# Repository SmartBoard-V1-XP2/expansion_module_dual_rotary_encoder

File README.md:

# Dual Encoder Module with ATtiny48

## Overview
This repository is dedicated to the design and implementation of a Dual Encoder Module, featuring two EC12E24204A8 encoders interfaced with an ATtiny48 microcontroller. Designed as an expansion module for the smartboard, it connects via a single smartboard connector, providing precise rotational input control for a wide range of applications.

## Key Features
- **Dual EC12E24204A8 Encoders**: High-quality rotary encoders for accurate and reliable input.
- **ATtiny48 Microcontroller**: Efficiently decodes and manages encoder signals.
- **SPI/UART Communication**: Offers flexible data transfer options to suit different requirements.
- **Smartboard Compatibility**: Easily integrates with smartboard systems through a dedicated connector.
- **Programmable via Connector Signals**: Enables easy programming and configuration.

### Schematic

*The schematic diagram provides a detailed view of the circuit design and component connections, essential for understanding the module's functionality and for troubleshooting.*

### Board Design - Top View

*This image shows the top view of the PCB layout, highlighting the placement of components, including the encoders and the ATtiny48 microcontroller.*

### Board Design - Bottom View

*The bottom view of the PCB layout illustrates the routing of traces and the arrangement of additional components, giving a complete overview of the PCB design.*

### Connector Signals

*This diagram details the signal configuration on the connector used to interface the module with a smartboard, outlining each pin's function and connectivity.*

## Contributions and Feedback
Contributions to this project are welcome. If you have suggestions for improvement or have developed additional features, please fork the repository, make your changes, and submit a pull request. For any questions or issues, please open an issue in the GitHub repository.

## License
This charger project is licensed under the MIT License with the following terms:

- **Permission to Use**: You are free to use, modify, and distribute this charger design in both private and commercial settings.
- **Attribution Requirement**: While not required, attribution to the original author, Adam Łuczak, is appreciated. This can be done through a citation or a link back to this repository.
- **No Warranty**: This design is provided "as is", without warranty of any kind. Use it at your own risk.
- **Liability**: The author is not liable for any damages or losses that may arise from the use of this design.

For the full terms and conditions, please refer to the MIT License documentation.

## Contact
Should you have any inquiries or suggestions regarding this charger project, please don't hesitate to contact Adam Łuczak at adam.luczak@outlook.com.

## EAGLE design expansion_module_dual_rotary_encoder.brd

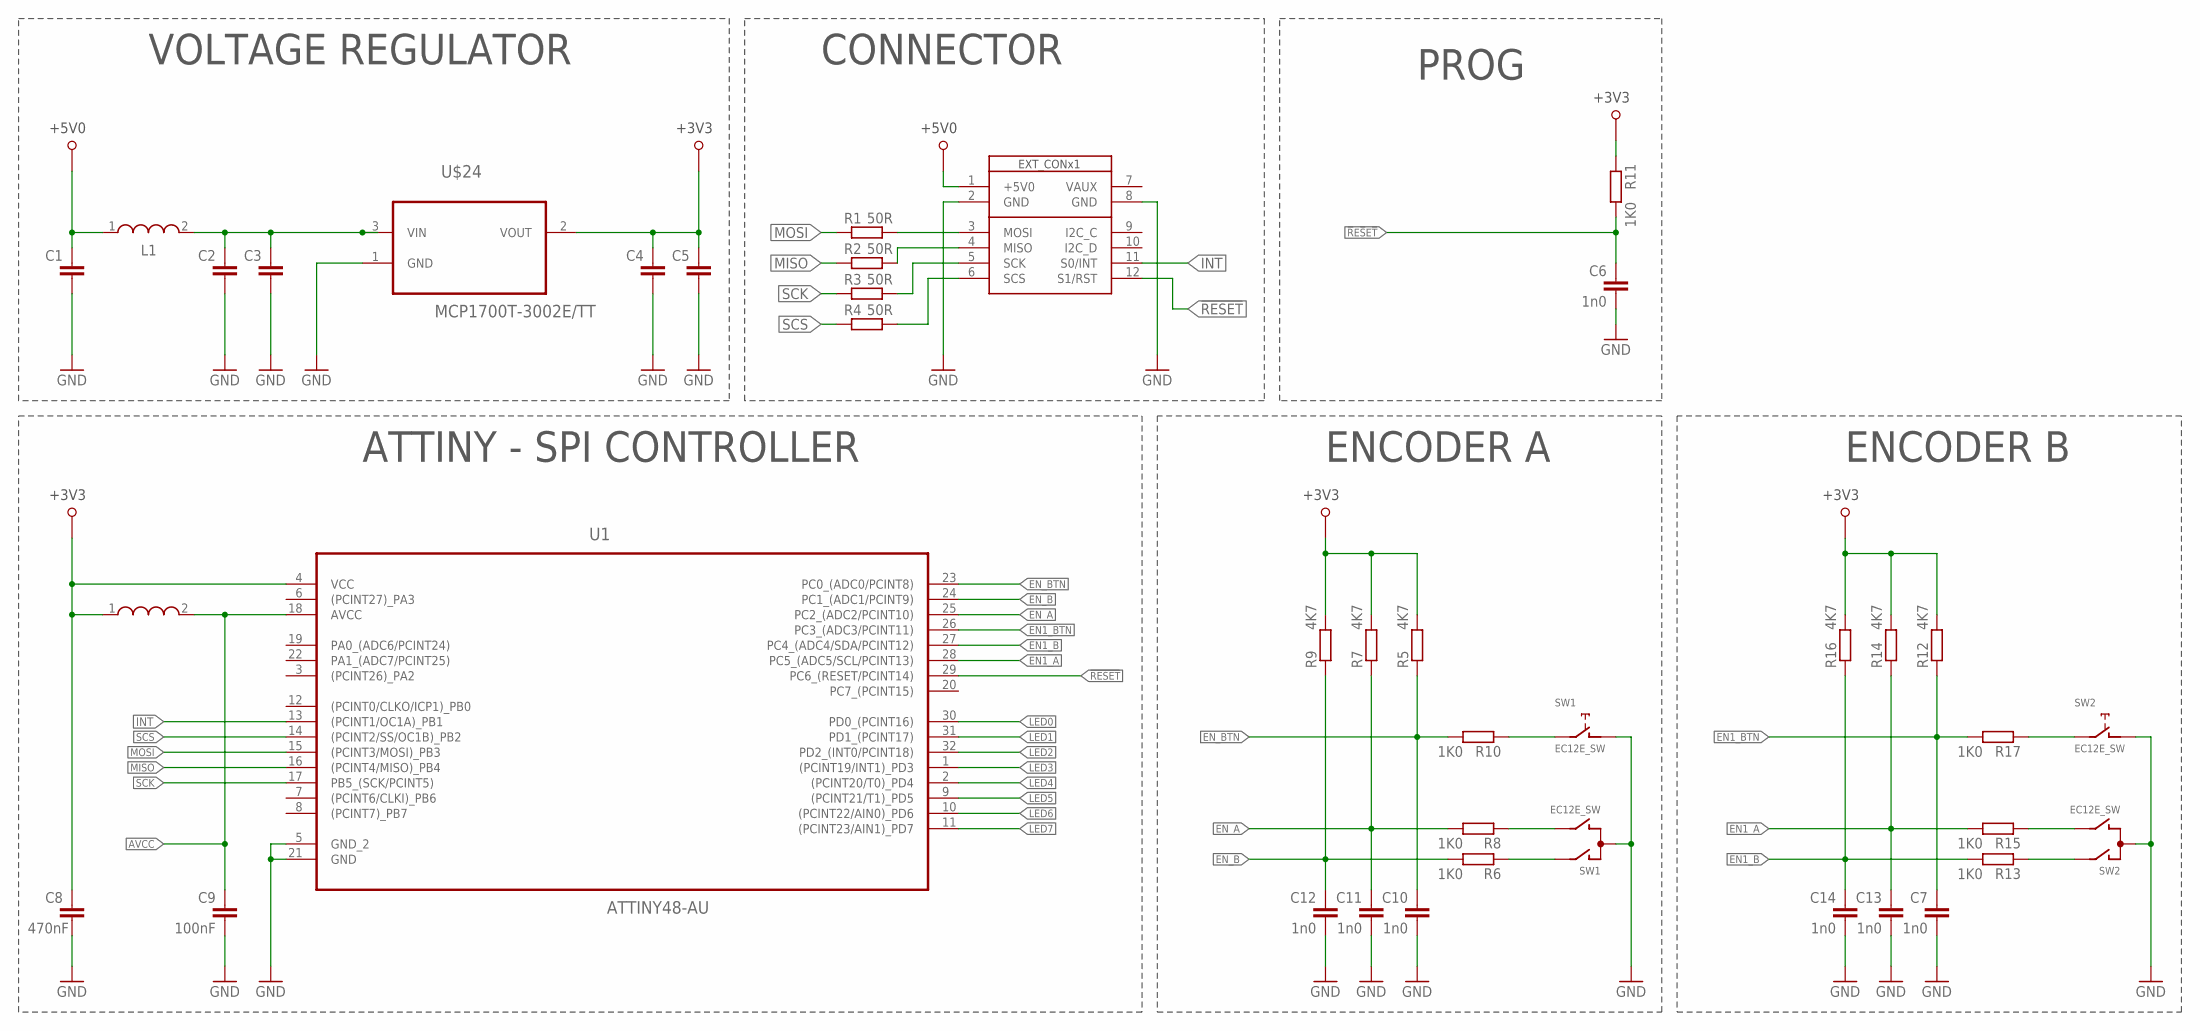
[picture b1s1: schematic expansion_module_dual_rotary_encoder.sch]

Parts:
C1, C2, C3, C4, C5: C-EUC0805; C0805
C6, C7, C10, C11, C12, C13, C14: 1n0; C0805
C8: 470nF; C0805
C9: 100nF; C0805
L1: WE-LQ_1210; WE-LQ_M
L2: WE-PMI_0805
R1, R2, R3, R4: 50R; R0805
R5, R7, R9, R12, R14, R16: 4K7; R0805
R6, R8, R10, R11, R13, R15, R17: 1K0; R0805
SW1, SW2: EC12E_SW; ALPS_EC12E_SW
U1: ATTINY48-AU; QFP80P900X900X120-32N
U$1: SB_EXT_CON_X1_SPI; SB_EXT_CON_X1_FULL
U$24: MCP1700T-3002E/TT; SOT95P237X112-3N

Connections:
!R!E!S!E!T: C6.2, R11.2
!RESET: U1.29 (PC6_(RESET/PCINT14)), U$1.12 (S1/RST)
+3V3: C4.2, C5.2, C8.2, L2.1, R5.2, R7.2, R9.2, R11.1, R12.2, R14.2, R16.2, U1.4 (VCC), U$24.2 (VOUT)
+5V0: C1.2, L1.1, U$1.1 (+5V0)
AVCC: C9.2, L2.2, U1.18 (AVCC)
EN1_A: C13.2, R14.1, R15.2, U1.28 (PC5_(ADC5/SCL/PCINT13))
EN1_B: C14.2, R13.2, R16.1, U1.27 (PC4_(ADC4/SDA/PCINT12))
EN1_BTN: C7.2, R12.1, R17.2, U1.26 (PC3_(ADC3/PCINT11))
EN_A: C11.2, R7.1, R8.2, U1.25 (PC2_(ADC2/PCINT10))
EN_B: C12.2, R6.2, R9.1, U1.24 (PC1_(ADC1/PCINT9))
EN_BTN: C10.2, R5.1, R10.2, U1.23 (PC0_(ADC0/PCINT8))
GND: C1.1, C2.1, C3.1, C4.1, C5.1, C6.1, C7.1, C8.1, C9.1, C10.1, C11.1, C12.1, C13.1, C14.1, SW1.C, SW1.D (1), SW2.C, SW2.D (1), U1.5 (GND_2), U1.21 (GND), U$1.2 (GND), U$1.8 (GND), U$24.1 (GND)
INT: U1.13 ((PCINT1/OC1A)_PB1), U$1.11 (S0/INT)
LED0: U1.30 (PD0_(PCINT16))
LED1: U1.31 (PD1_(PCINT17))
LED2: U1.32 (PD2_(INT0/PCINT18))
LED3: U1.1 ((PCINT19/INT1)_PD3)
LED4: U1.2 ((PCINT20/T0)_PD4)
LED5: U1.9 ((PCINT21/T1)_PD5)
LED6: U1.10 ((PCINT22/AIN0)_PD6)
LED7: U1.11 ((PCINT23/AIN1)_PD7)
MISO: R2.1, U1.16 ((PCINT4/MISO)_PB4)
MOSI: R1.1, U1.15 ((PCINT3/MOSI)_PB3)
unnamed: R1.2, U$1.3 (MOSI)
unnamed: R2.2, U$1.4 (MISO)
unnamed: R3.2, U$1.5 (SCK)
unnamed: R4.2, U$1.6 (SCS)
unnamed: R6.1, SW1.A
unnamed: R13.1, SW2.A
unnamed: C2.2, C3.2, L1.2, U$24.3 (VIN)
unnamed: R15.1, SW2.B
unnamed: R8.1, SW1.B
unnamed: R10.1, SW1.E (2)
unnamed: R17.1, SW2.E (2)
SCK: R3.1, U1.17 (PB5_(SCK/PCINT5))
SCS: R4.1, U1.14 ((PCINT2/SS/OC1B)_PB2)

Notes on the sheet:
CONNECTOR
VOLTAGE REGULATOR
ATTINY - SPI CONTROLLER
ENCODER A
PROG
ENCODER B

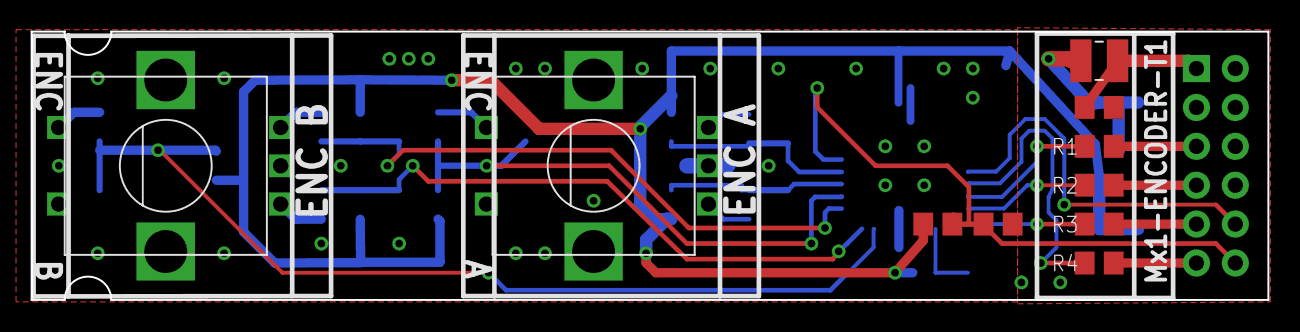
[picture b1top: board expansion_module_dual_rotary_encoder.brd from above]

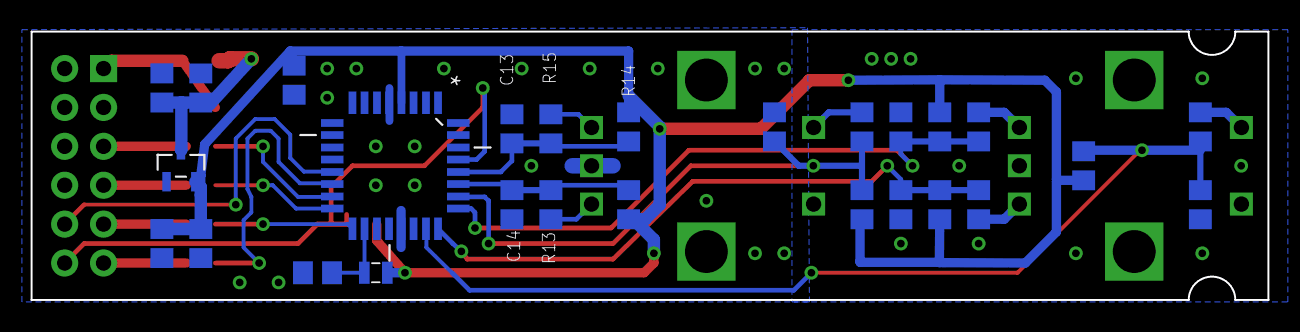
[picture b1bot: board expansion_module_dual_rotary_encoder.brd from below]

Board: 2 copper layers, 80.8 x 17.5 mm, 38 parts (27 on the bottom side), 28 nets.

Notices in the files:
README.md:
License: MIT
parts and their libraries:
EagleLibrary_Wuerth_Elektronik_eiSos_rev: Copyright: Würth Elektronik
